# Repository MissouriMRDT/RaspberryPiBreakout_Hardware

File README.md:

# RaspberryPiBreakout_Hardware
A power shield for the Raspberry Pi to be used for network management applications.

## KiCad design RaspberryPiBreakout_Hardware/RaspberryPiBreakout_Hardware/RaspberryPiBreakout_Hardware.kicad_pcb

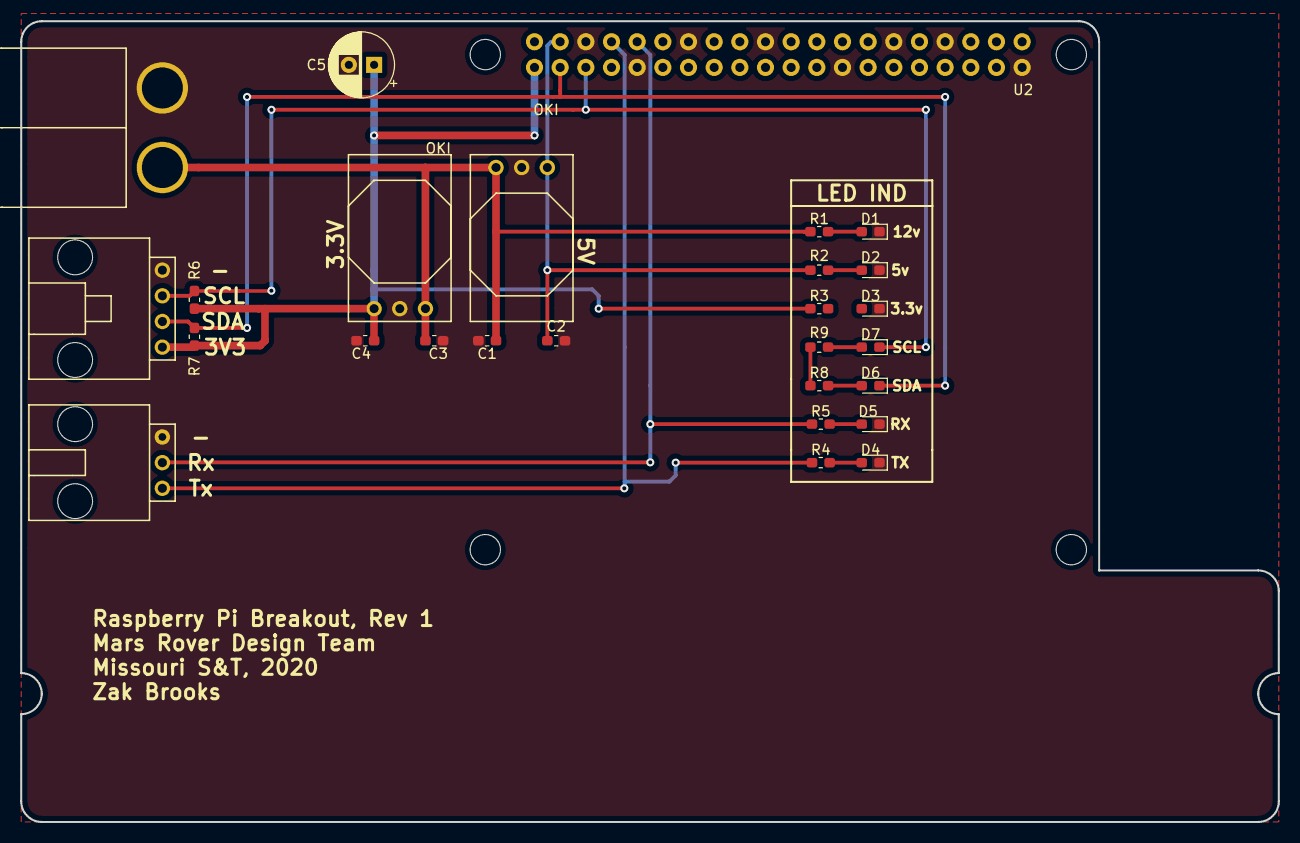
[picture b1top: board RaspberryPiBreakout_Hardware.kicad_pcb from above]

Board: 2 copper layers, 124.5 x 79.2 mm, 27 parts (0 on the bottom side), 15 nets.

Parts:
C1, C2, C3, C4: 10u; C_0603_1608Metric_Pad1.05x0.95mm_HandSolder
C5: CP1; CP_Radial_D6.3mm_P2.50mm
Conn1: AndersonPP; Anderson_2_Horizontal_Side_by_Side
Conn2: Molex_SL_03; MOLEX_SL_03_Horizontal
Conn3: Molex_SL_04; MOLEX_SL_04_Horizontal
D1, D2, D3, D4, D5, D6, D7: LED; D_0603_1608Metric_Pad1.05x0.95mm_HandSolder
R1: 1k; R_0603_1608Metric_Pad1.05x0.95mm_HandSolder
R2, R3, R4, R5, R8, R9: 500; R_0603_1608Metric_Pad1.05x0.95mm_HandSolder
R6, R7: 4.7k; R_0603_1608Metric_Pad1.05x0.95mm_HandSolder
U1, U3: OKI; OKI_Horizontal
U2: Raspberry_Pi; RaspberryPi_THT_BOTTOM

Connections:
+3V3: C4.1, C5.1, Conn3.1, R3.1, R6.1, R7.1, R8.1, R9.1, U2.1, U2.17, U3.3
+5V: C2.1, R2.1, U1.3, U2.2, U2.4
+12V: C1.1, C3.1, Conn1.2, R1.1, U1.1, U3.1
GND: C1.2, C2.2, C3.2, C4.2, C5.2, Conn1.1, Conn2.3, Conn3.4, D1.1, D2.1, D3.1, D4.1, D5.1, U1.2, U2.6, U2.9, U2.14, U2.20, U2.25, U2.30, U2.34, U2.39, U3.2
unnamed: D1.2, R1.2
unnamed: D2.2, R2.2
unnamed: D3.2, R3.2
unnamed: D4.2, R4.2
unnamed: D5.2, R5.2
unnamed: D6.2, R8.2
unnamed: D7.2, R9.2
SCL1: Conn3.3, D7.1, R6.2, U2.5
SDA1: Conn3.2, D6.1, R7.2, U2.3
Serial_Rx: Conn2.2, R5.1, U2.10
Serial_Tx: Conn2.1, R4.1, U2.8

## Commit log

2019-02-28 created schematic
2019-02-28 Created Netlist
2019-02-28 finished Layout
2019-02-28 generated gerbs
2019-02-28 Fixed Gerbs
2019-09-21 Added 3.3v oki and molex
2019-09-21 Added serial flag and serial molex
2019-09-21 same thing
2019-09-21 annotated, net list, high level placement
2019-09-21 Added LED ind and gen new net list
2019-09-21 High level layout placement
2019-09-21 Updated tx/rx pinouts and added resistor molex
2019-09-21 Began traces
2019-09-21 Layout and traces complete
2019-09-21 added 2 new leds
2019-09-21 added silkscreens
2019-09-28 layout and schematic changes
2019-09-28 finished updating layout
2019-09-28 Gerbs
2019-09-28 zipped gerbs
2019-12-04 Revert "Gerbs"
    This reverts commit 0bdd6a63055cf1f667c7f4bdde6934c7b1ab89a0.
2019-12-04 Revert "zipped gerbs"
    This reverts commit e59478fae635c6a636ef2db83d9d04212a3128c1.
2019-12-04 Added 5v OKI back to the layout
2019-12-05 Wired up
2019-12-13 Added another set of LiDar
2019-12-13 Layout differences?
2019-12-13 Cut 3v3 and changed lidar to pow gnd signal(s)
2019-12-14 Theoretically done board
2019-12-14 Added Gerbs
2019-12-15 Uploaded BOM
2020-11-03 Recommited Rev3 of the board
2020-11-03 Reverted to rev3
2020-11-03 Added gerbs to rev3
2020-11-03 Revert "Recommited Rev3 of the board"
    This reverts commit 41c7ae642d3903a82f2d95ade2c09fb429966cfe.
